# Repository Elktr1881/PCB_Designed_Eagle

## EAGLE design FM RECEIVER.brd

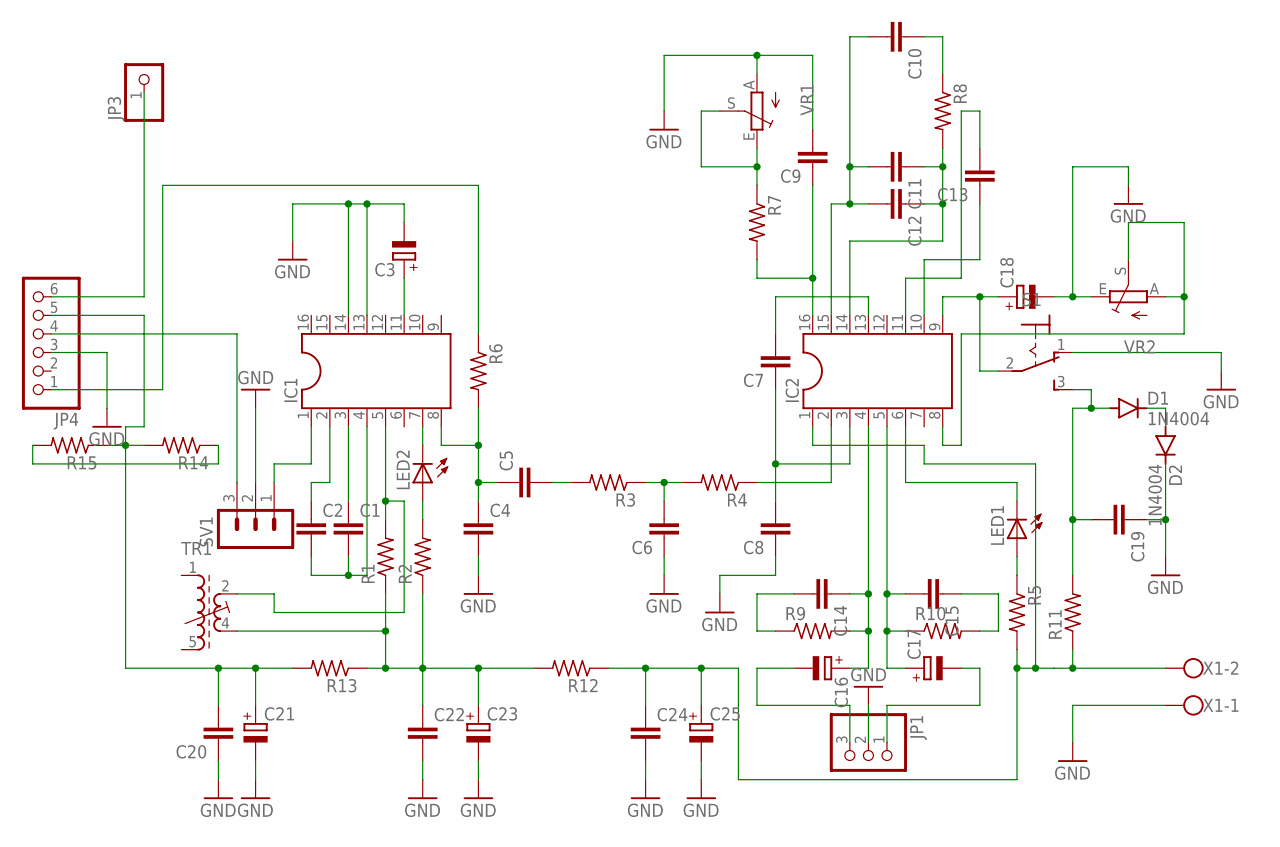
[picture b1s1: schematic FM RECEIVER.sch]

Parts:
C1, C2, C4, C5, C6, C7, C8, C9, C10, C11, C12, C13, C14, C15, C19, C20, C22, C24: C-EU050-025X075; C050-025X075
C3, C16, C17, C18, C21, C23, C25: CPOL-EUE2,5-6E; E2,5-6E
D1, D2: 1N4004; DO41-10
IC1, IC2: DIL16
JP1: PINHD-1X3; 1X03
JP3: PINHD-1X1; 1X01
JP4: PINHD-1X6; 1X06
LED1, LED2: LED3MM
R1, R2, R3, R4, R5, R6, R7, R8, R9, R10, R11, R12, R13, R14, R15: R-US_0207/10; 0207/10
S1: 320-916
SV1: MA03-1
TR1: 71-4-1542; 71-5
VR1, VR2: TRIM_EU-CA6V; CA6V
X1: W237-102

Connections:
GND: C3.-, C4.2, C6.1, C8.1, C9.2, C18.-, C19.1, C20.1, C21.-, C22.2, C23.-, C24.2, C25.-, D2.C, IC1.13, IC1.14, JP1.2, JP4.3, S1.1 (O), SV1.2, VR1.A, VR2.E, X1.1
unnamed: IC1.7, LED2.K (C)
unnamed: LED2.A, R2.2
unnamed: C1.1, IC1.3
unnamed: C2.1, IC1.2
unnamed: C1.2, C2.2, IC1.4
unnamed: IC1.5, R1.2, TR1.2 (A2)
unnamed: JP4.4, SV1.3
unnamed: C15.1, R10.2
unnamed: C20.2, C21.+, JP4.5, R13.2, R14.2, R15.1
unnamed: C4.1, C5.1, IC1.8, R6.2
unnamed: C14.2, R9.1
unnamed: C5.2, R3.2
unnamed: C6.2, R3.1, R4.2
unnamed: IC2.2, R4.1
unnamed: C14.1, C16.+, IC2.4, R9.2
unnamed: C7.1, C8.2, IC2.3
unnamed: IC1.1, SV1.1
unnamed: C15.2, C17.+, IC2.5, R10.1
unnamed: C24.1, C25.+, IC2.1, R5.2, R11.1, R12.1, X1.2
unnamed: D1.C, D2.A
unnamed: C22.1, C23.+, R1.1, R2.1, R12.2, R13.1, TR1.4 (E2)
unnamed: C19.2, D1.A, R11.2, S1.3 (S)
unnamed: IC2.6, LED1.K (C)
unnamed: LED1.A, R5.1
unnamed: C11.1, C12.1, IC2.14, R8.2
unnamed: C18.+, IC2.9, S1.2
unnamed: IC2.8, VR2.A, VR2.S
unnamed: C13.2, IC2.11
unnamed: C13.1, IC2.10
unnamed: C16.-, JP1.3
unnamed: C10.2, C11.2, C12.2, IC2.15
unnamed: C17.-, JP1.1
unnamed: C10.1, R8.1
unnamed: C9.1, IC2.16, R7.2
unnamed: C3.+, IC1.11
unnamed: R7.1, VR1.E, VR1.S
unnamed: JP3.1, JP4.6
unnamed: JP4.1, R6.1
unnamed: R14.1, R15.2
unnamed: C7.2, IC2.13

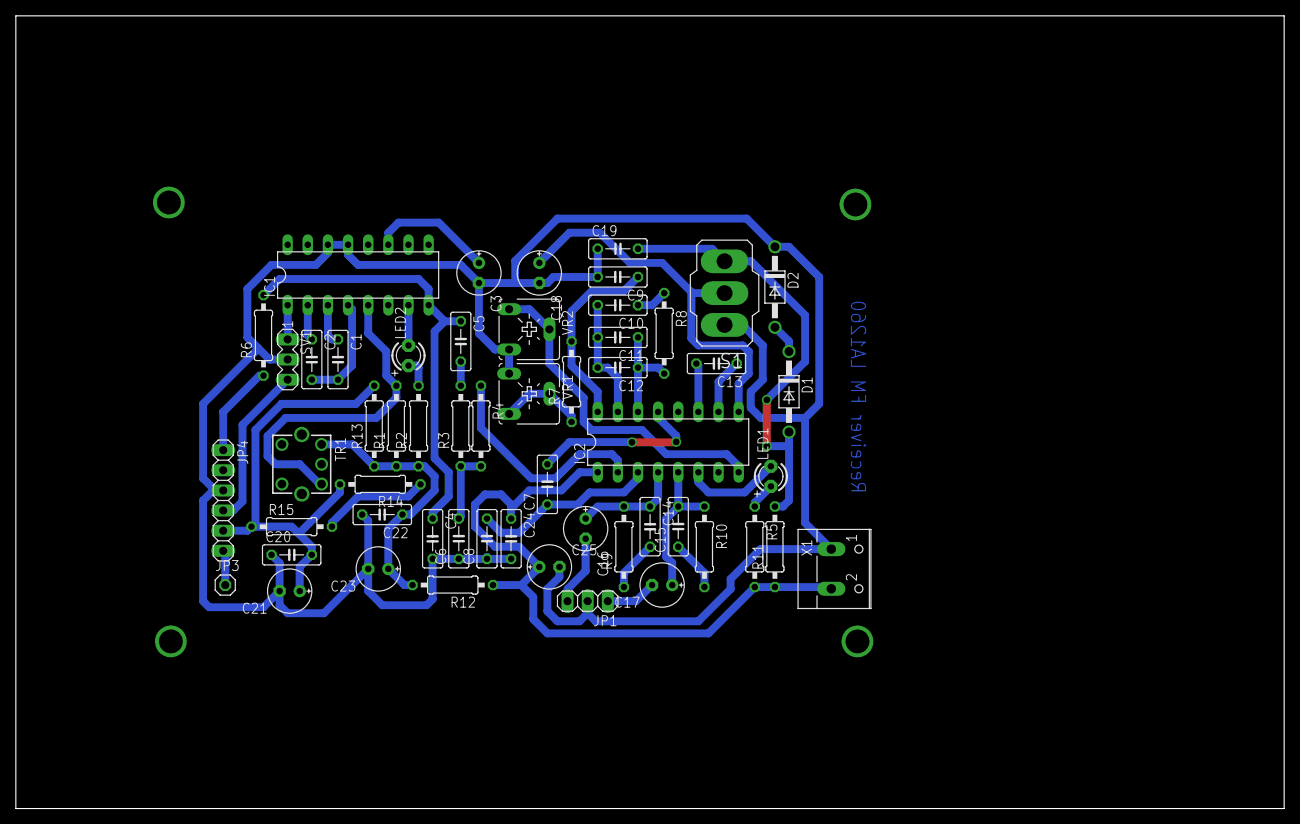
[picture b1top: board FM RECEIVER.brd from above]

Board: 2 copper layers, 160.0 x 100.0 mm, 55 parts (0 on the bottom side), 41 nets.

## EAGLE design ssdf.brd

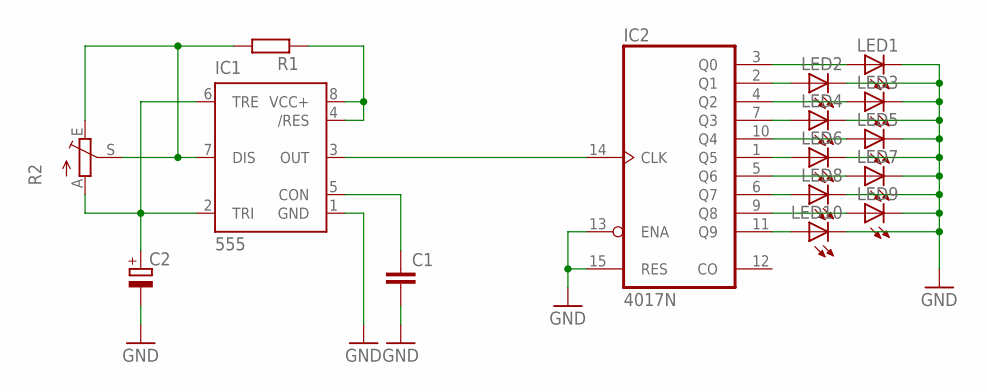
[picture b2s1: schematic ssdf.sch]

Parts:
C1: C-EU050-025X075; C050-025X075
C2: CPOL-EUE2-5; E2-5
IC1: 555; DIP08-KIT
IC2: 4017N; DIL16
LED1, LED2, LED3, LED4, LED5, LED6, LED7, LED8, LED9, LED10: LED3MM
R1: R-EU_0204/7; 0204/7
R2: TRIM_EU-B25P; B25P

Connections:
GND: C1.2, C2.-, IC1.1 (GND), IC2.13 (ENA), IC2.15 (RES), LED1.K (C), LED2.K (C), LED3.K (C), LED4.K (C), LED5.K (C), LED6.K (C), LED7.K (C), LED8.K (C), LED9.K (C), LED10.K (C)
unnamed: C2.+, IC1.2 (TRI), IC1.6 (TRE), R2.A
unnamed: C1.1, IC1.5 (CON)
unnamed: IC1.4 (/RES), IC1.8 (VCC+), R1.1
unnamed: IC1.7 (DIS), R1.2, R2.E, R2.S
unnamed: IC2.3 (Q0), LED1.A
unnamed: IC2.2 (Q1), LED2.A
unnamed: IC2.4 (Q2), LED3.A
unnamed: IC2.7 (Q3), LED4.A
unnamed: IC2.10 (Q4), LED5.A
unnamed: IC2.1 (Q5), LED6.A
unnamed: IC2.5 (Q6), LED7.A
unnamed: IC2.6 (Q7), LED8.A
unnamed: IC2.9 (Q8), LED9.A
unnamed: IC2.11 (Q9), LED10.A
unnamed: IC1.3 (OUT), IC2.14 (CLK)
VDD: IC2.16 (VDD)
VSS: IC2.8 (VSS)

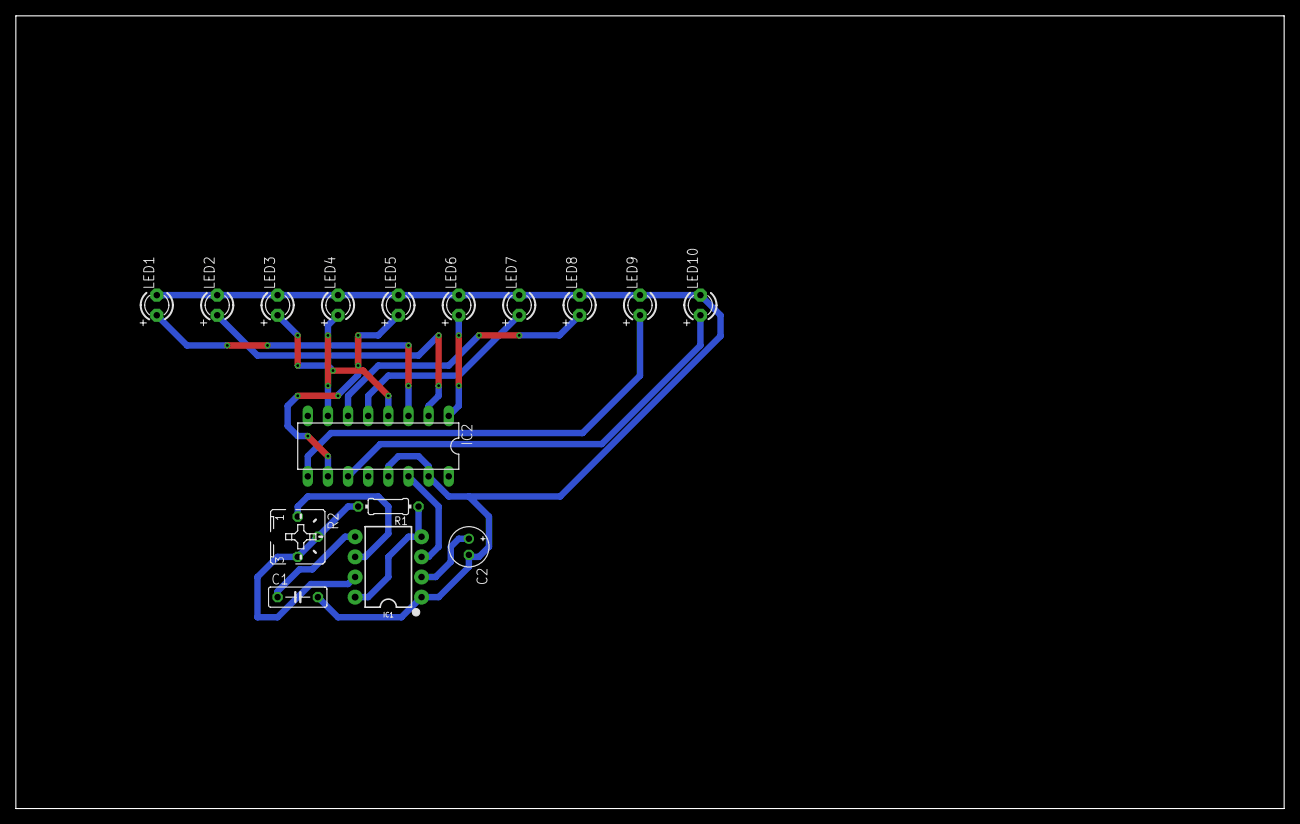
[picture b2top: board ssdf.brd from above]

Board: 2 copper layers, 160.0 x 100.0 mm, 16 parts (0 on the bottom side), 16 nets.

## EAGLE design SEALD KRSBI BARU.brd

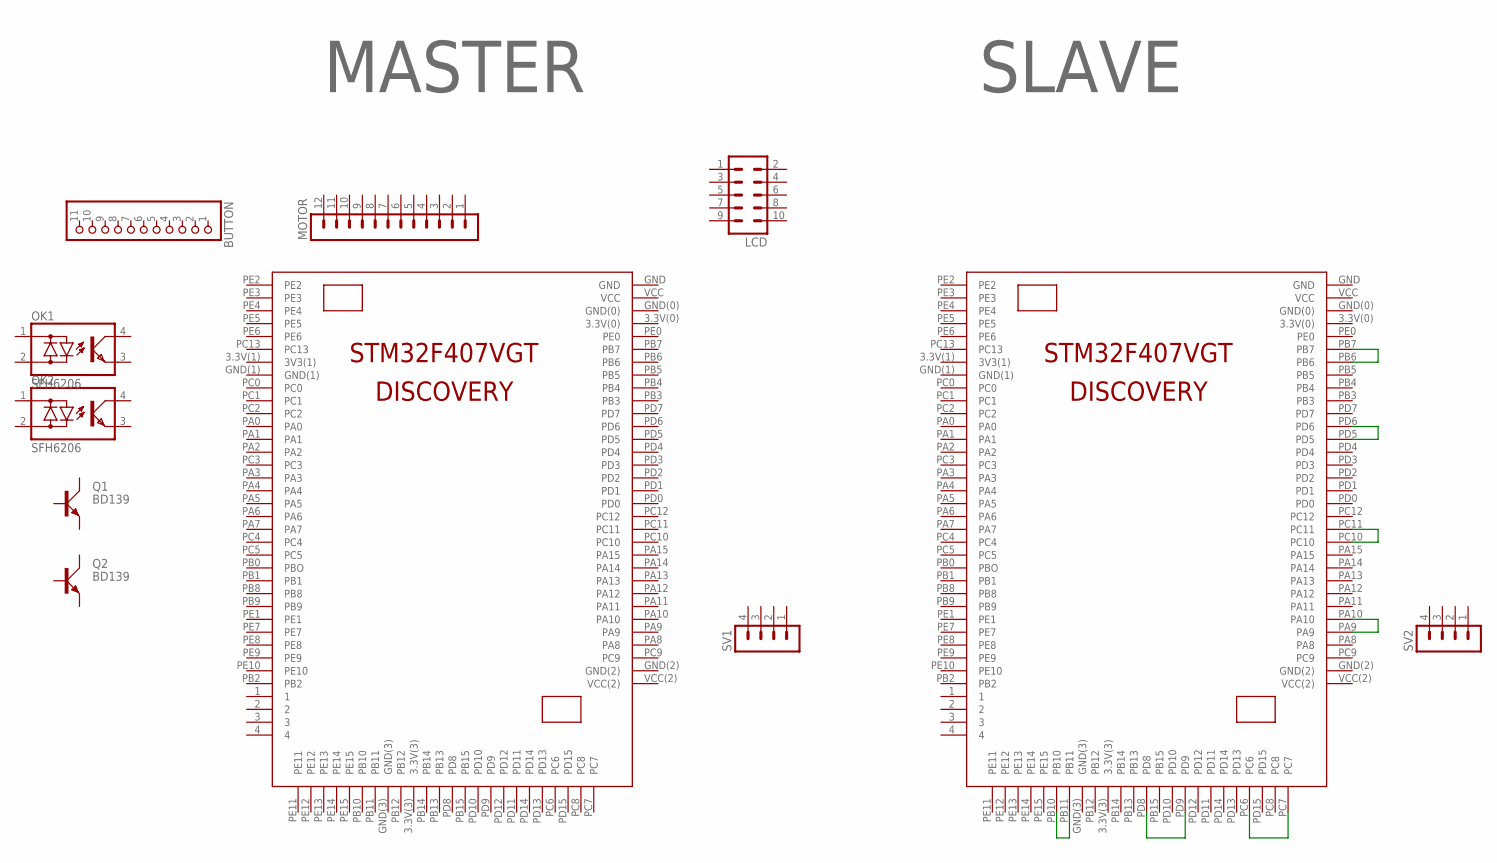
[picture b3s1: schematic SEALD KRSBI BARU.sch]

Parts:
BUTTON: PINHD-1X11; 1X11
LCD: MA05-2
MOTOR: MA12-1
OK1, OK2: SFH6206; DIL4-SMD
Q1, Q2: BD139; TO126AV
SV1, SV2: MA04-1
U$1, U$2: STM32F407(BOARD); STM32F407VGT

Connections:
unnamed: U$1.PB10, U$1.PB11
unnamed: U$1.PD8, U$1.PD9
unnamed: U$1.PC6, U$1.PC7
unnamed: U$1.PA9, U$1.PA10
unnamed: U$1.PC10, U$1.PC11
unnamed: U$1.PD5, U$1.PD6
unnamed: U$1.PB6, U$1.PB7

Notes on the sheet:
MASTER
SLAVE

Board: 2 copper layers, 11 parts (0 on the bottom side), 7 nets, no tracks yet.

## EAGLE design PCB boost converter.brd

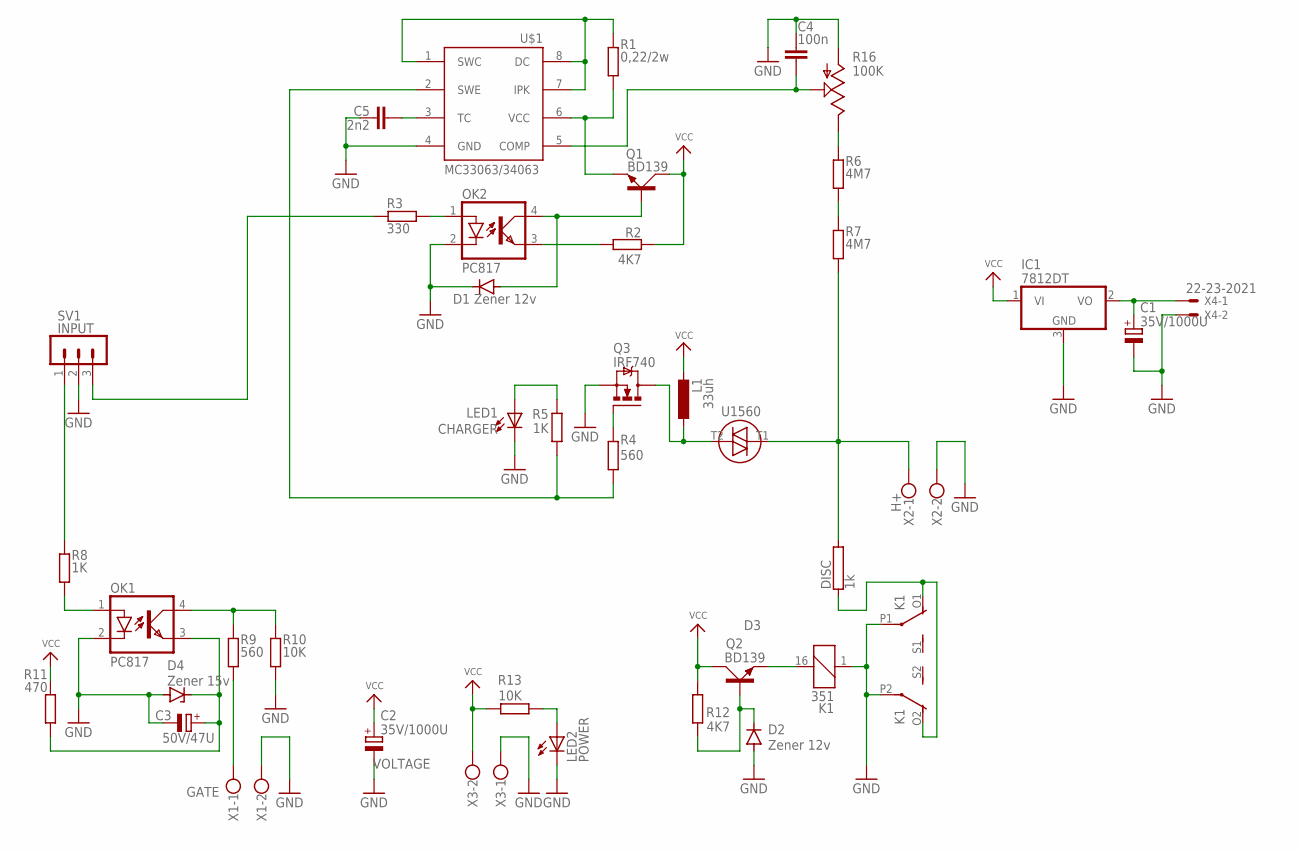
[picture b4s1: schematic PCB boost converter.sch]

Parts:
C1, C2: 35V/1000U; E2,5-7
C3: 50V/47U; 153CLV-0810
C4: 100n; C0805K
C5: 2n2; C0805K
D1, D2: Zener 12v; DO35-7
D3: U1560; BR210S
D4: Zener 15v; DO35Z10
DISC: 1k; RWM10X64
IC1: 7812DT; TO252
K1: 351
L1: 33uh; TJ3-U2
LED1: CHARGER; LED_1206
LED2: POWER; LED_1206
OK1, OK2: PC817; DIL04
Q1, Q2: BD139; TO126AV
Q3: IRF740; TO220BV
R1: 0,22/2w; M1206
R2, R12: 4K7; M1206
R3: 330; M1206
R4, R9: 560; M1206
R5, R8: 1K; M1206
R6, R7: 4M7; 0309/10
R10, R13: 10K; M1206
R11: 470; M1206
R16: 100K; CA6V
SV1: INPUT; MA03-1
U$1: MC33063/MC34063D; SO08
X1: GATE; W237-102
X2: H+; W237-102
X3: VOLTAGE; W237-102
X4: 22-23-2021

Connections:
GND: C1.-, C2.-, C3.-, C4.1, C5.1, D1.C, D2.A, D4.A, IC1.3 (GND), K1.1, K1.P1, K1.P2, LED1.C, LED2.C, OK1.2 (C), OK2.2 (C), Q3.S, R10.1, R16.A, SV1.2, U$1.4 (GND), X1.2, X2.2, X3.1, X4.2
unnamed: R1.2, U$1.1 (SWC), U$1.7 (IPK), U$1.8 (DC)
unnamed: Q1.E, R1.1, U$1.6 (VCC)
unnamed: D1.A, OK2.4 (COL), Q1.B
unnamed: OK2.3 (EMIT), R2.2
unnamed: R8.1, SV1.1
unnamed: OK2.1 (A), R3.2
unnamed: D3.T2, L1.1, Q3.D
unnamed: C4.2, R16.S, U$1.5 (COMP)
unnamed: D3.T1, DISC.2, R7.1, X2.1
unnamed: C5.2, U$1.3 (TC)
unnamed: LED1.A, R5.2
unnamed: R6.1, R7.2
unnamed: Q3.G, R4.1
unnamed: R3.1, SV1.3
unnamed: R6.2, R16.E
unnamed: DISC.1, K1.O1 (O), K1.O2 (O)
unnamed: OK1.1 (A), R8.2
unnamed: OK1.4 (COL), R9.2, R10.2
unnamed: K1.16 (2), Q2.E
unnamed: C3.+, D4.C, OK1.3 (EMIT), R11.1
unnamed: D2.C, Q2.B, R12.1
unnamed: R9.1, X1.1
unnamed: LED2.A, R13.1
unnamed: R4.2, R5.1, U$1.2 (SWE)
unnamed: C1.+, IC1.2 (VO), X4.1
VCC: C2.+, IC1.1 (VI), L1.2, Q1.C, Q2.C, R2.1, R11.2, R12.2, R13.2, X3.2

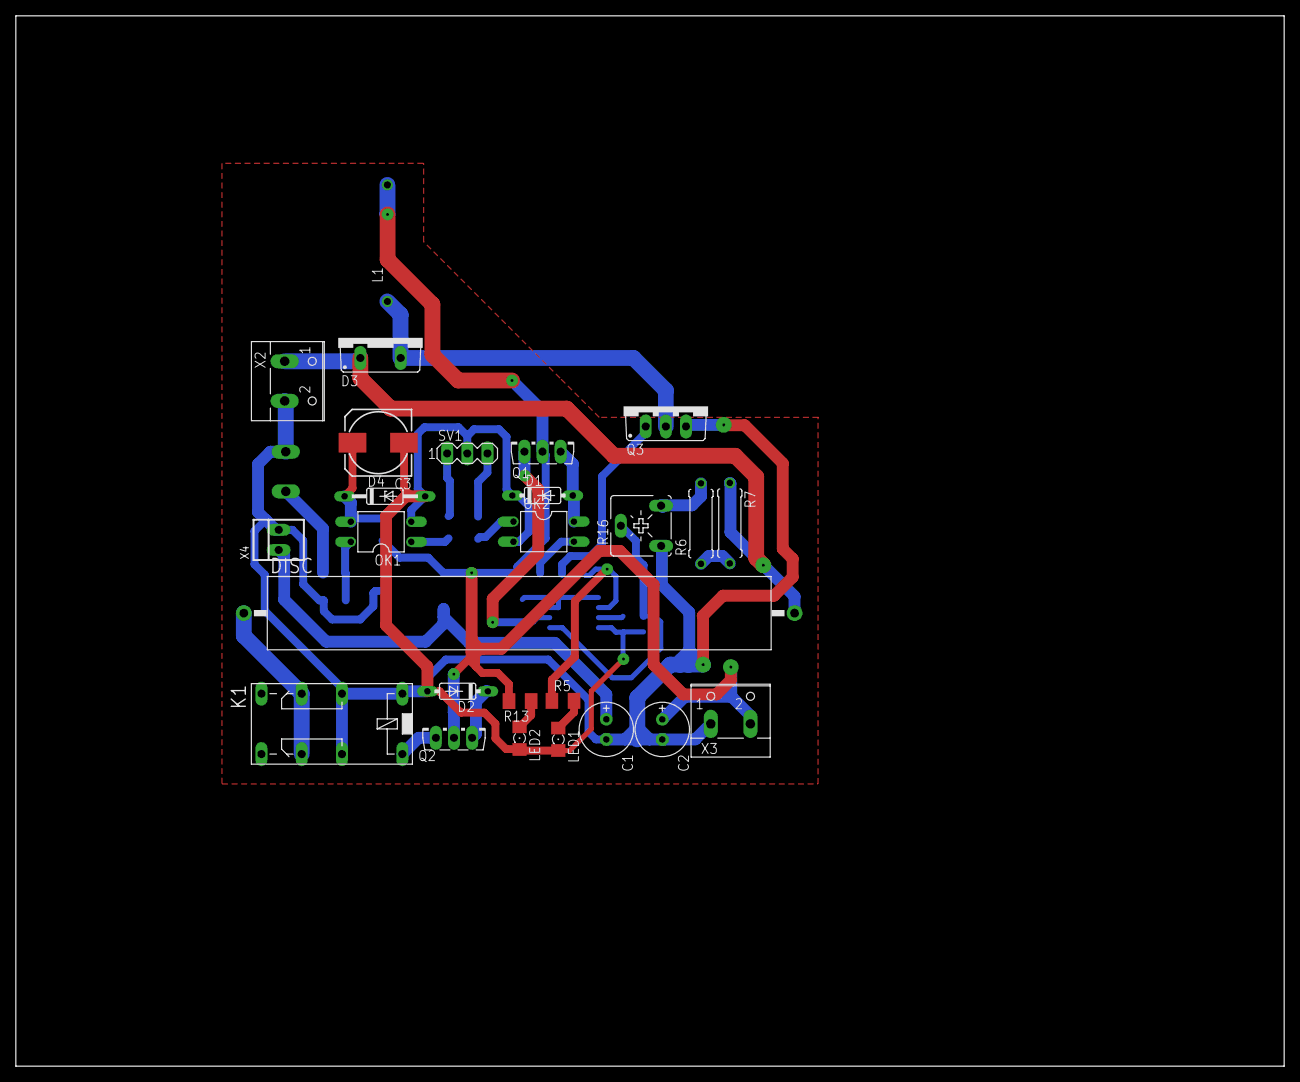
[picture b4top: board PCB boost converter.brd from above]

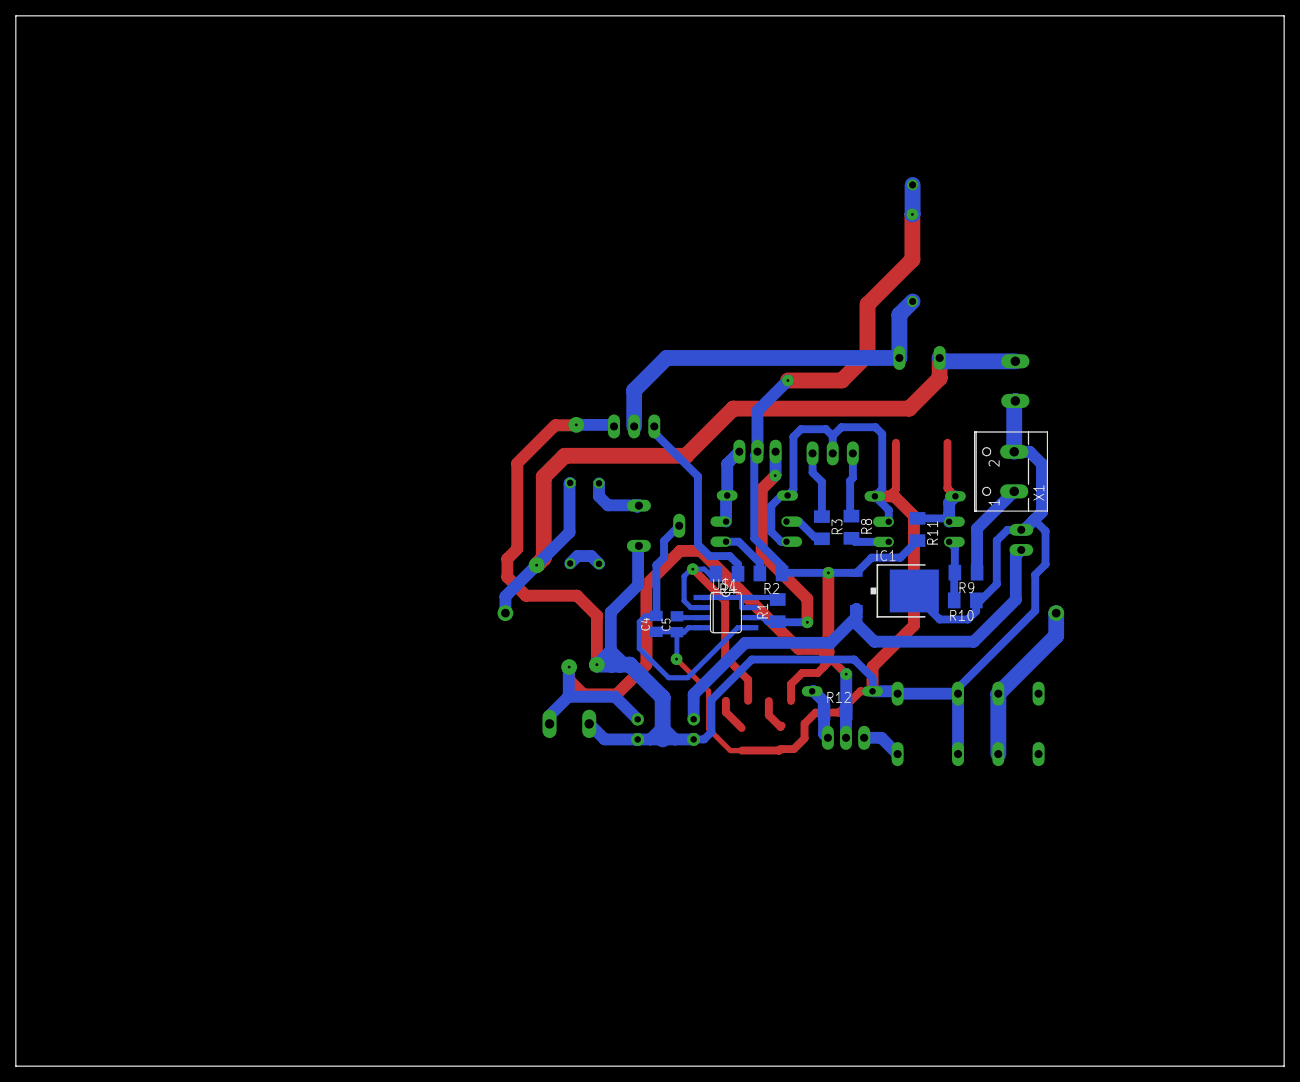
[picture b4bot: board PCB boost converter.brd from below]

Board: 2 copper layers, 160.0 x 132.5 mm, 40 parts (14 on the bottom side), 27 nets.

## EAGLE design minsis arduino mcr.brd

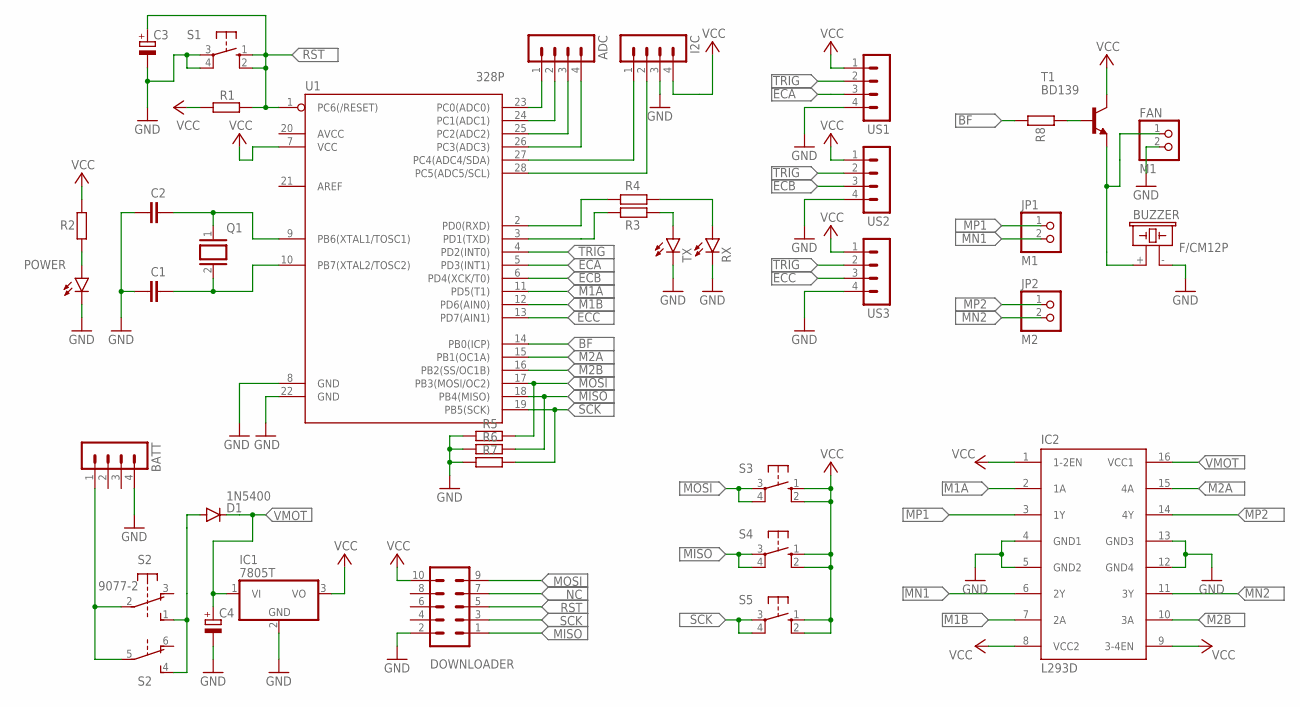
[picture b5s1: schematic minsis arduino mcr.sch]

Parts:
ADC: MA04-1
BATT: MA04-1
BUZZER: F/CM12P
C1, C2: C-EU050-024X044; C050-024X044
C3: CPOL-EUE2,5-6E; E2,5-6E
C4: CPOL-EUE3.5-8; E3,5-8
D1: 1N5400; DO201-15
DOWNLOADER: MA05-2
FAN: M1; 1X02
I2C: MA04-1
IC1: 7805T; TO220H
IC2: L293D; DIL16
JP1: M1; 1X02
JP2: M2; 1X02
POWER: LED3MM
Q1: XTAL/S; QS
R1, R2, R3, R4, R5, R6, R7, R8: R-EU_0207/7; 0207/7
RX: LED3MM
S1, S3, S4, S5: 10-XX; B3F-10XX
S2: 9077-2
T1: BD139; TO126
TX: LED3MM
U1: 328P; DIP28
US1, US2, US3: MA04-1

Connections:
BF: R8.2, U1.14 (PB0(ICP))
ECA: U1.5 (PD3(INT1)), US1.3
ECB: U1.6 (PD4(XCK/T0)), US2.3
ECC: U1.13 (PD7(AIN1)), US3.3
GND: BATT.4, BUZZER.- (2), C1.1, C2.1, C3.-, C4.-, DOWNLOADER.2, FAN.2, I2C.3, IC1.2 (GND), IC2.4 (GND1), IC2.5 (GND2), IC2.12 (GND4), IC2.13 (GND3), POWER.K (C), R5.1, R6.1, R7.1, RX.K (C), S1.3, S1.4 (P1), TX.K (C), U1.8 (GND), U1.22 (GND), US1.4, US2.4, US3.4
M1A: IC2.2 (1A), U1.11 (PD5(T1))
M1B: IC2.7 (2A), U1.12 (PD6(AIN0))
M2A: IC2.15 (4A), U1.15 (PB1(OC1A))
M2B: IC2.10 (3A), U1.16 (PB2(SS/OC1B))
MISO: DOWNLOADER.1, R6.2, S4.3, S4.4 (P1), U1.18 (PB4(MISO))
MN1: IC2.6 (2Y), JP1.2
MN2: IC2.11 (3Y), JP2.2
MOSI: DOWNLOADER.9, R5.2, S3.3, S3.4 (P1), U1.17 (PB3(MOSI/OC2))
MP1: IC2.3 (1Y), JP1.1
MP2: IC2.14 (4Y), JP2.1
unnamed: R4.1, RX.A
unnamed: R3.1, TX.A
unnamed: R4.2, U1.2 (PD0(RXD))
unnamed: R3.2, U1.3 (PD1(TXD))
unnamed: POWER.A, R2.1
unnamed: C2.2, Q1.1, U1.9 (PB6(XTAL1/TOSC1))
unnamed: C1.2, Q1.2, U1.10 (PB7(XTAL2/TOSC2))
unnamed: BATT.1, S2.2, S2.5
unnamed: D1.A, S2.1 (S), S2.4 (S)
unnamed: BUZZER.+ (1), FAN.1, T1.1 (E)
unnamed: R8.1, T1.3 (B)
unnamed: ADC.1, U1.23 (PC0(ADC0))
unnamed: ADC.2, U1.24 (PC1(ADC1))
unnamed: ADC.3, U1.25 (PC2(ADC2))
unnamed: ADC.4, U1.26 (PC3(ADC3))
unnamed: I2C.1, U1.27 (PC4(ADC4/SDA))
unnamed: I2C.2, U1.28 (PC5(ADC5/SCL))
NC: DOWNLOADER.7
RST: C3.+, DOWNLOADER.5, R1.2, S1.1 (S), S1.2 (S1), U1.1 (PC6(/RESET))
SCK: DOWNLOADER.3, R7.2, S5.3, S5.4 (P1), U1.19 (PB5(SCK))
TRIG: U1.4 (PD2(INT0)), US1.2, US2.2, US3.2
VCC: DOWNLOADER.10, I2C.4, IC1.3 (VO), IC2.1 (1-2EN), IC2.8 (VCC2), IC2.9 (3-4EN), R1.1, R2.2, S3.1 (S), S3.2 (S1), S4.1 (S), S4.2 (S1), S5.1 (S), S5.2 (S1), T1.2 (C), U1.7 (VCC), US1.1, US2.1, US3.1
VMOT: C4.+, D1.C, IC1.1 (VI), IC2.16 (VCC1)

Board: 2 copper layers, 37 parts (0 on the bottom side), 37 nets, no tracks yet.

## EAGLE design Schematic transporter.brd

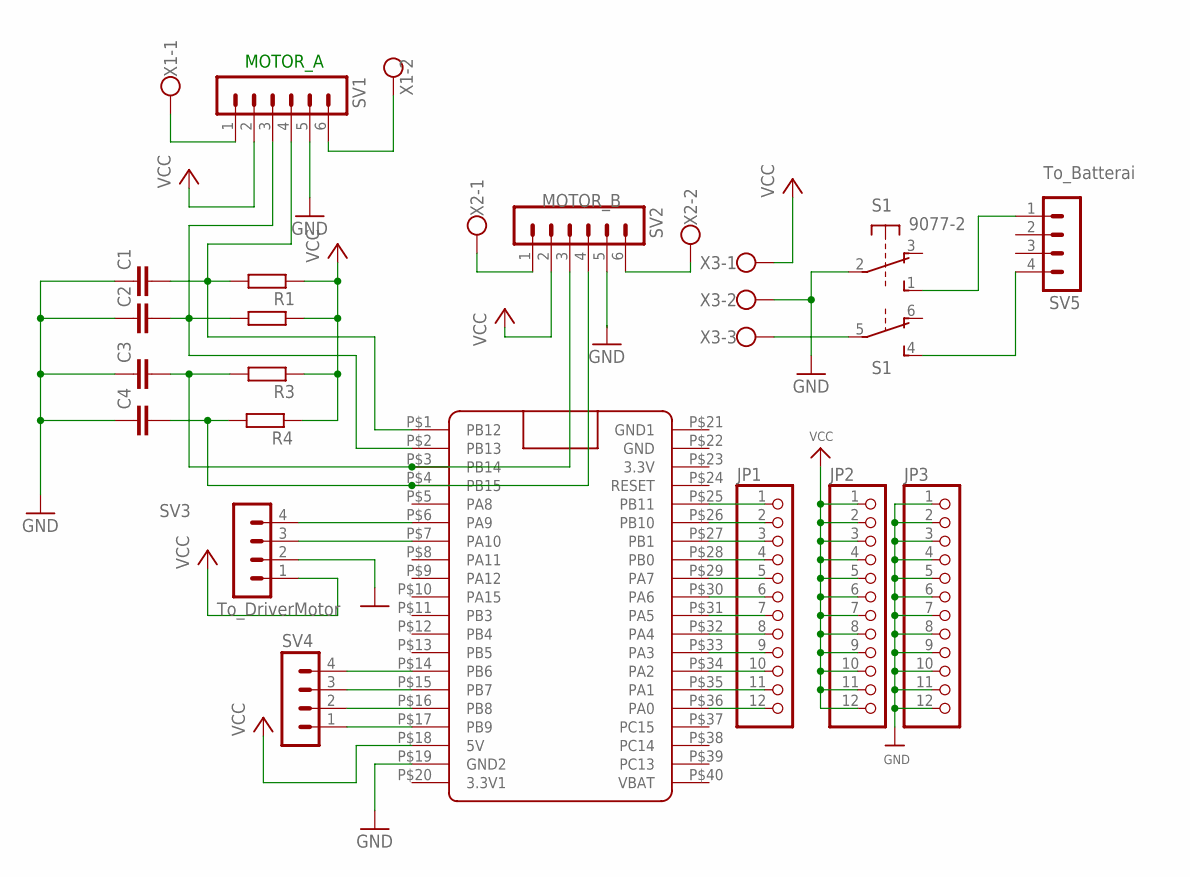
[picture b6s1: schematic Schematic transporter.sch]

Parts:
C1, C2, C3, C4: C-EU050-024X044; C050-024X044
JP1, JP2, JP3: PINHD-1X12; 1X12
R1, R2, R3, R4: R-EU_0207/7; 0207/7
S1: 9077-2
SV1, SV2: MA06-1
SV3, SV4, SV5: MA04-1
U$1: BLUE_PILL
X1, X2: W237-102
X3: W237-103

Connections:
GND: C1.1, C2.1, C3.1, C4.1, JP3.1, JP3.2, JP3.3, JP3.4, JP3.5, JP3.6, JP3.7, JP3.8, JP3.9, JP3.10, JP3.11, JP3.12, S1.2, SV1.5, SV2.5, SV3.2, U$1.P$19 (GND2), X3.2
GND1: U$1.P$21 (GND1)
unnamed: JP1.1, U$1.P$25 (PB11)
unnamed: JP1.2, U$1.P$26 (PB10)
unnamed: JP1.3, U$1.P$27 (PB1)
unnamed: JP1.4, U$1.P$28 (PB0)
unnamed: JP1.5, U$1.P$29 (PA7)
unnamed: JP1.6, U$1.P$30 (PA6)
unnamed: JP1.7, U$1.P$31 (PA5)
unnamed: JP1.8, U$1.P$32 (PA4)
unnamed: JP1.9, U$1.P$33 (PA3)
unnamed: JP1.10, U$1.P$34 (PA2)
unnamed: JP1.11, U$1.P$35 (PA1)
unnamed: JP1.12, U$1.P$36 (PA0)
unnamed: C1.2, R1.2, SV1.4, U$1.P$1 (PB12)
unnamed: C2.2, R2.1, SV1.3, U$1.P$2 (PB13)
unnamed: C3.2, R3.2, SV2.3, U$1.P$3 (PB14)
unnamed: C4.2, R4.2, SV2.4, U$1.P$4 (PB15)
unnamed: SV3.4, U$1.P$6 (PA9)
unnamed: SV3.3, U$1.P$7 (PA10)
unnamed: SV4.4, U$1.P$14 (PB6)
unnamed: SV2.6, X2.2
unnamed: SV1.1, X1.1
unnamed: SV2.1, X2.1
unnamed: SV1.6, X1.2
unnamed: SV4.3, U$1.P$15 (PB7)
unnamed: SV4.2, U$1.P$16 (PB8)
unnamed: SV4.1, U$1.P$17 (PB9)
unnamed: S1.5, X3.3
unnamed: S1.1 (S), SV5.1
unnamed: S1.4 (S), SV5.4
VCC: JP2.1, JP2.2, JP2.3, JP2.4, JP2.5, JP2.6, JP2.7, JP2.8, JP2.9, JP2.10, JP2.11, JP2.12, R1.1, R2.2, R3.1, R4.1, SV1.2, SV2.2, SV3.1, U$1.P$18 (5V), X3.1

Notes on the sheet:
To_Batterai
MOTOR_A
MOTOR_B
To_DriverMotor

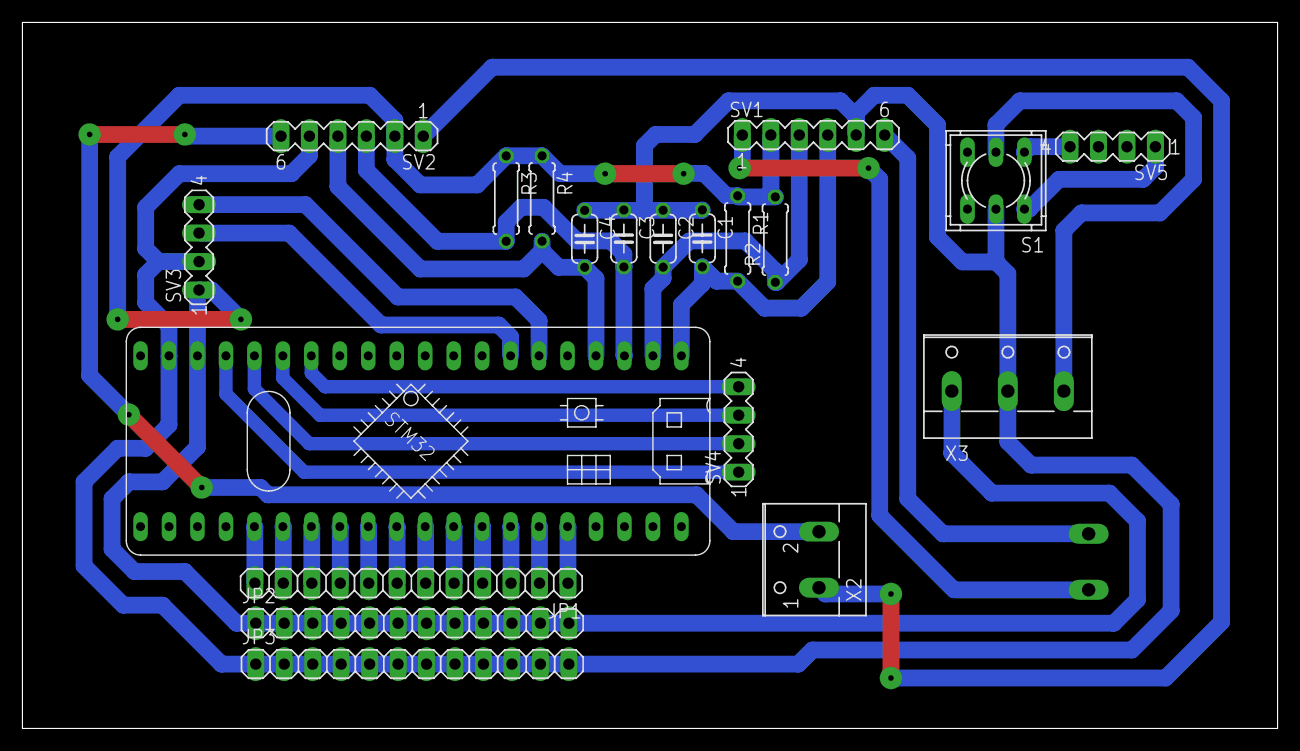
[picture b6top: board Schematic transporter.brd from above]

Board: 2 copper layers, 112.0 x 63.0 mm, 21 parts (1 on the bottom side), 31 nets.

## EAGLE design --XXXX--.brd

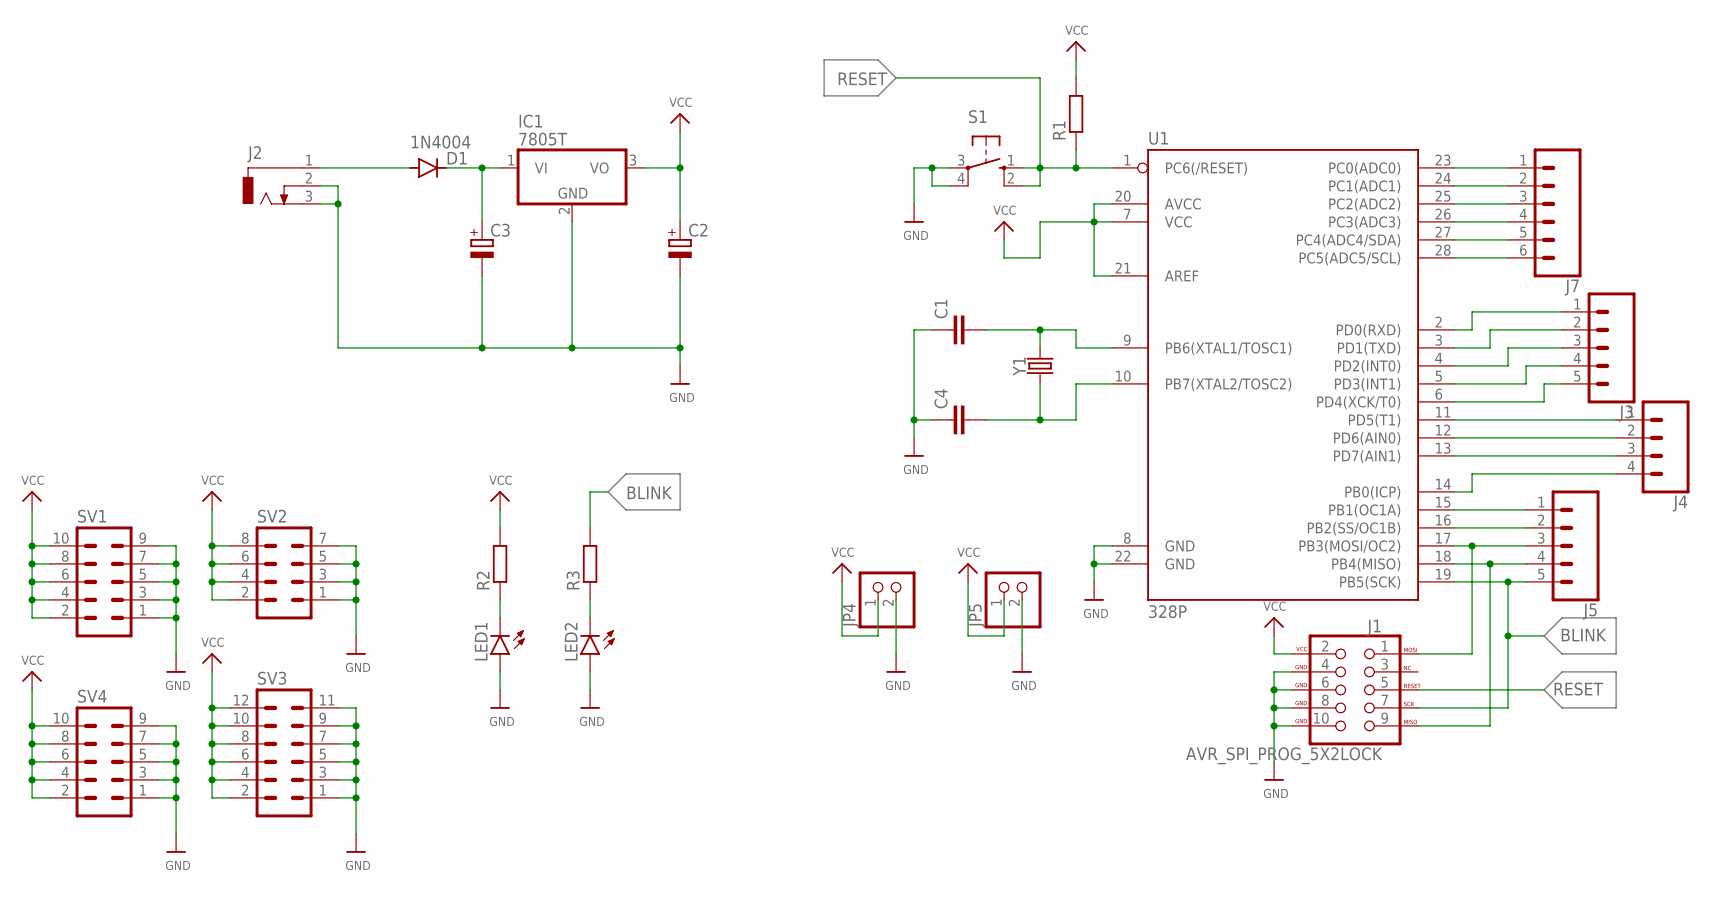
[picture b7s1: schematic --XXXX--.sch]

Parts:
C1, C4: C-EU050-024X044; C050-024X044
C2: CPOL-EUE2.5-5; E2,5-5
C3: CPOL-EUE2.5-7; E2,5-7
D1: 1N4004; DO41-10
IC1: 7805T; TO220H
J1: AVR_SPI_PROG_5X2LOCK; 2X5-SHROUDED_LOCK
J2: DCJ0303
J3, J5: CONN_05; 1X05
J4: CONN_04; 1X04
J7: CONN_06SILK_FEMALE_PTH; 1X06
JP4, JP5: PINHD-1X2; 1X02
LED1, LED2: LED3MM
R1, R2, R3: R-EU_0207/10; 0207/10
S1: 10-XX; B3F-10XX
SV1, SV4: MA05-2
SV2: MA04-2
SV3: MA06-2
U1: 328P; DIP28
Y1: CRYSTALPTH-HC49UV; HC49U

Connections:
BLINK: J1.7 (SCK), J5.5, R3.2, U1.19 (PB5(SCK))
GND: C1.1, C2.-, C3.-, C4.1, IC1.2 (GND), J1.4 (GND), J1.6 (GND), J1.8 (GND), J1.10 (GND), J2.2, J2.3, JP4.2, JP5.2, LED1.A, LED2.A, S1.3, S1.4 (P1), SV1.1, SV1.3, SV1.5, SV1.7, SV1.9, SV2.1, SV2.3, SV2.5, SV2.7, SV3.1, SV3.3, SV3.5, SV3.7, SV3.9, SV3.11, SV4.1, SV4.3, SV4.5, SV4.7, SV4.9, U1.8 (GND), U1.22 (GND)
unnamed: J7.1, U1.23 (PC0(ADC0))
unnamed: J7.2, U1.24 (PC1(ADC1))
unnamed: J7.3, U1.25 (PC2(ADC2))
unnamed: J7.4, U1.26 (PC3(ADC3))
unnamed: J7.5, U1.27 (PC4(ADC4/SDA))
unnamed: J7.6, U1.28 (PC5(ADC5/SCL))
unnamed: J3.1, U1.2 (PD0(RXD))
unnamed: J3.2, U1.3 (PD1(TXD))
unnamed: J3.3, U1.4 (PD2(INT0))
unnamed: J3.4, U1.5 (PD3(INT1))
unnamed: J3.5, U1.6 (PD4(XCK/T0))
unnamed: J4.1, U1.11 (PD5(T1))
unnamed: J4.2, U1.12 (PD6(AIN0))
unnamed: J4.3, U1.13 (PD7(AIN1))
unnamed: J4.4, U1.14 (PB0(ICP))
unnamed: J5.1, U1.15 (PB1(OC1A))
unnamed: J5.2, U1.16 (PB2(SS/OC1B))
unnamed: J1.1 (MOSI), J5.3, U1.17 (PB3(MOSI/OC2))
unnamed: J1.9 (MISO), J5.4, U1.18 (PB4(MISO))
unnamed: D1.A, J2.1
unnamed: C1.2, U1.9 (PB6(XTAL1/TOSC1)), Y1.2
unnamed: C4.2, U1.10 (PB7(XTAL2/TOSC2)), Y1.1
unnamed: LED1.K (C), R2.1
unnamed: C3.+, D1.C, IC1.1 (VI)
unnamed: LED2.K (C), R3.1
RESET: J1.5 (RESET), R1.1, S1.1 (S), S1.2 (S1), U1.1 (PC6(/RESET))
VCC: C2.+, IC1.3 (VO), J1.2 (VCC), JP4.1, JP5.1, R1.2, R2.2, SV1.2, SV1.4, SV1.6, SV1.8, SV1.10, SV2.2, SV2.4, SV2.6, SV2.8, SV3.2, SV3.4, SV3.6, SV3.8, SV3.10, SV3.12, SV4.2, SV4.4, SV4.6, SV4.8, SV4.10, U1.7 (VCC), U1.20 (AVCC), U1.21 (AREF)

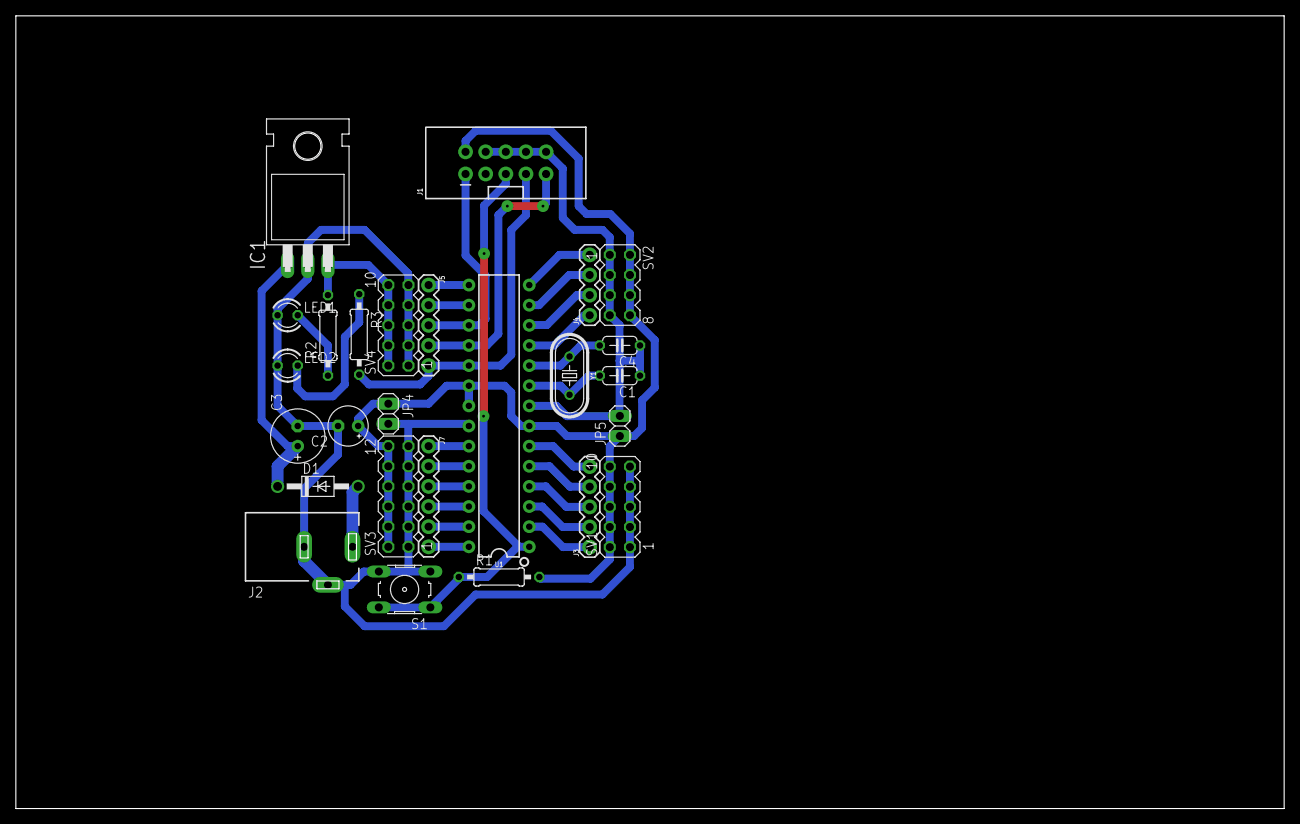
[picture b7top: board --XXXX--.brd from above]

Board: 2 copper layers, 160.0 x 100.0 mm, 26 parts (0 on the bottom side), 29 nets.

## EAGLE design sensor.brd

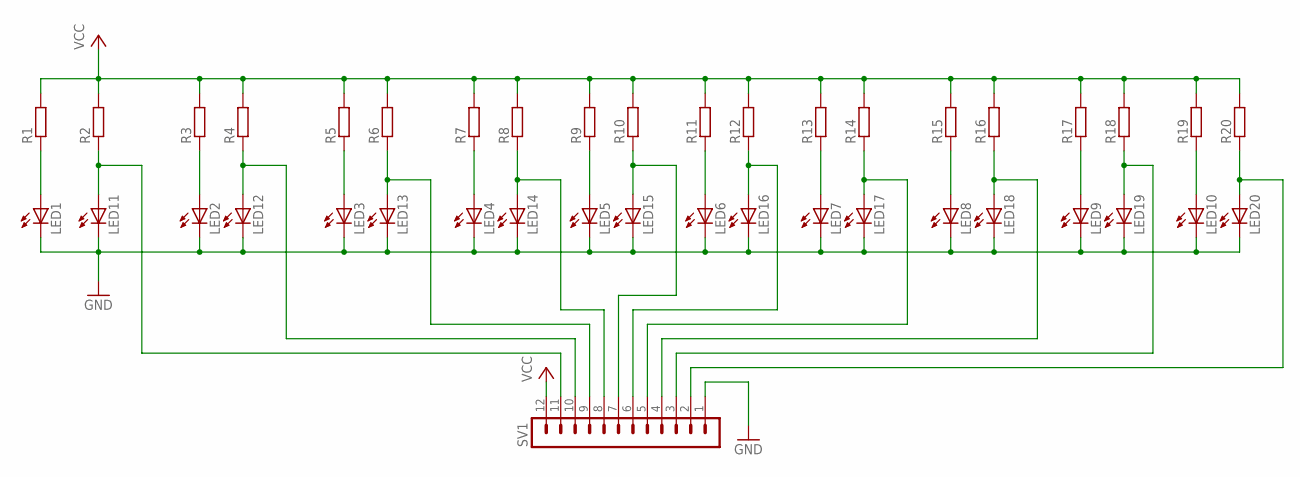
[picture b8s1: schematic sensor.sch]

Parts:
LED1, LED2, LED3, LED4, LED5, LED6, LED7, LED8, LED9, LED10, LED11, LED12, LED13, LED14, LED15, LED16, LED17, LED18, LED19, LED20: LED3MM
R1, R2, R3, R4, R5, R6, R7, R8, R9, R10, R11, R12, R13, R14, R15, R16, R17, R18, R19, R20: R-EU_0207/7; 0207/7
SV1: MA12-1

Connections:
GND: LED1.K (C), LED2.K (C), LED3.K (C), LED4.K (C), LED5.K (C), LED6.K (C), LED7.K (C), LED8.K (C), LED9.K (C), LED10.K (C), LED11.K (C), LED12.K (C), LED13.K (C), LED14.K (C), LED15.K (C), LED16.K (C), LED17.K (C), LED18.K (C), LED19.K (C), LED20.K (C), SV1.1
unnamed: LED1.A, R1.1
unnamed: LED11.A, R2.1, SV1.11
unnamed: LED2.A, R3.1
unnamed: LED12.A, R4.1, SV1.10
unnamed: LED3.A, R5.1
unnamed: LED13.A, R6.1, SV1.9
unnamed: LED4.A, R7.1
unnamed: LED14.A, R8.1, SV1.8
unnamed: LED5.A, R9.1
unnamed: LED15.A, R10.1, SV1.7
unnamed: LED6.A, R11.1
unnamed: LED16.A, R12.1, SV1.6
unnamed: LED20.A, R20.1, SV1.2
unnamed: LED10.A, R19.1
unnamed: LED19.A, R18.1, SV1.3
unnamed: LED9.A, R17.1
unnamed: LED18.A, R16.1, SV1.4
unnamed: LED8.A, R15.1
unnamed: LED17.A, R14.1, SV1.5
unnamed: LED7.A, R13.1
VCC: R1.2, R2.2, R3.2, R4.2, R5.2, R6.2, R7.2, R8.2, R9.2, R10.2, R11.2, R12.2, R13.2, R14.2, R15.2, R16.2, R17.2, R18.2, R19.2, R20.2, SV1.12

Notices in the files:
parts and their libraries:
SparkFun-Connectors: Licensing: Creative Commons ShareAlike 4.0 International - https://creativecommons.org/licenses/by-sa/4.0
